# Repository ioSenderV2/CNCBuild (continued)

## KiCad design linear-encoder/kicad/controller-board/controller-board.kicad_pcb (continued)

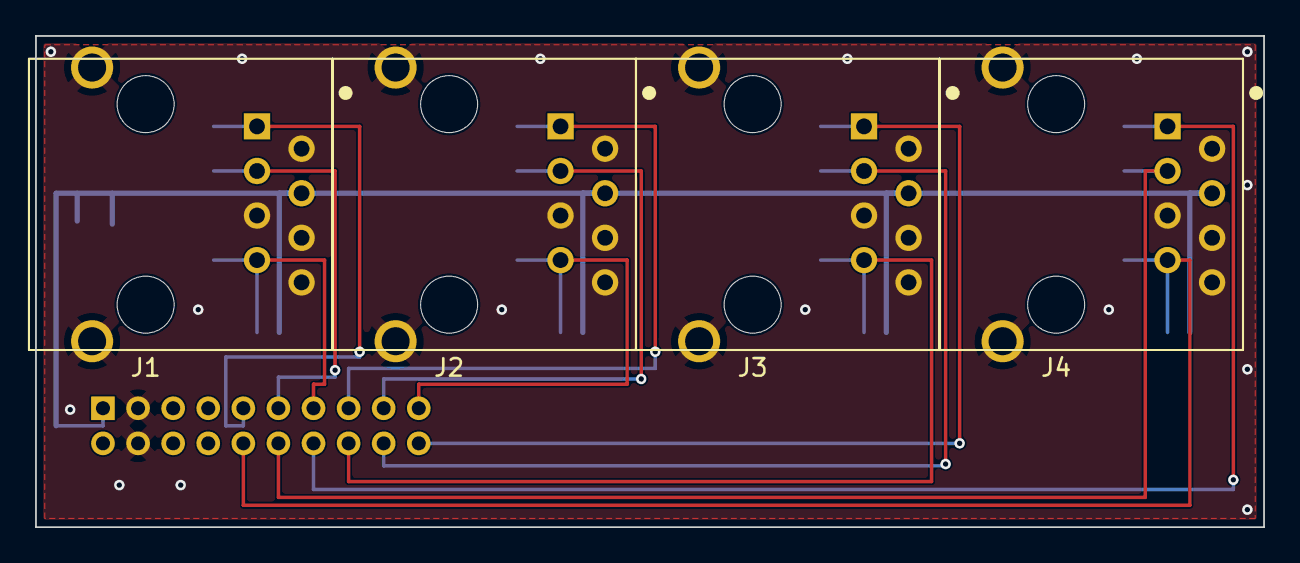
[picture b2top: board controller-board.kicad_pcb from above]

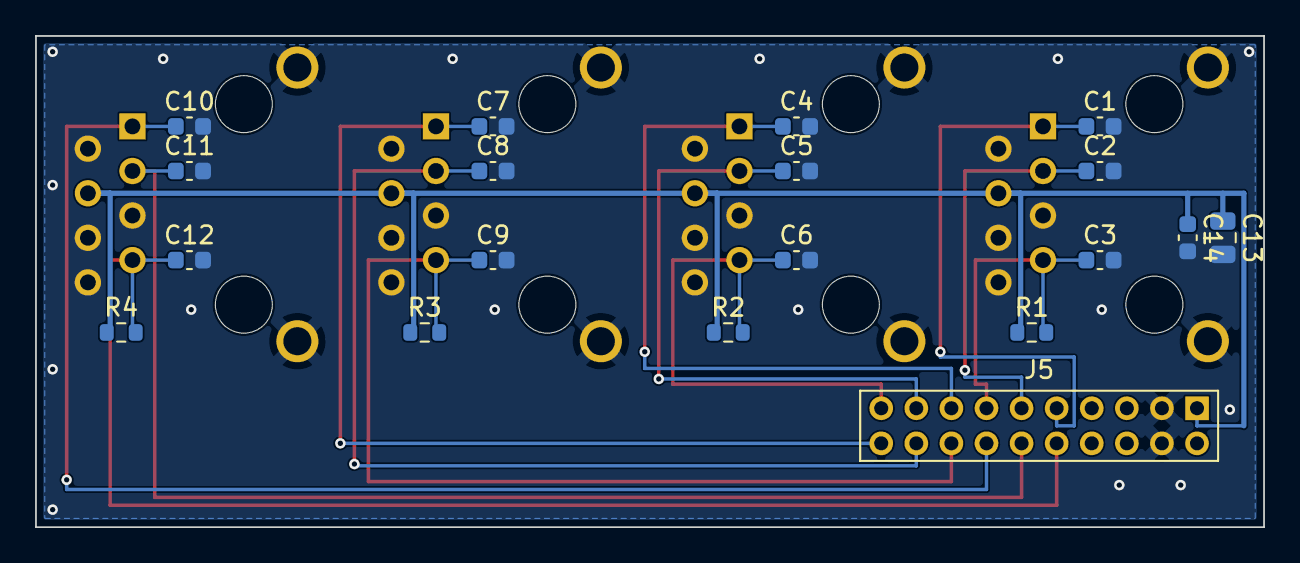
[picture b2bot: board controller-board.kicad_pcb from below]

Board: 2 copper layers, 70.0 x 28.0 mm, 23 parts (19 on the bottom side), 14 nets.

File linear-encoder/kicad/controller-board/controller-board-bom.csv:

"Refs","Value","Footprint","Qty","DNP"
"C1","1n","Capacitor_SMD:C_0603_1608Metric","1",""
"C2","1n","Capacitor_SMD:C_0603_1608Metric","1",""
"C3","1n","Capacitor_SMD:C_0603_1608Metric","1",""
"C4","1n","Capacitor_SMD:C_0603_1608Metric","1",""
"C5","1n","Capacitor_SMD:C_0603_1608Metric","1",""
"C6","1n","Capacitor_SMD:C_0603_1608Metric","1",""
"C7","1n","Capacitor_SMD:C_0603_1608Metric","1",""
"C8","1n","Capacitor_SMD:C_0603_1608Metric","1",""
"C9","1n","Capacitor_SMD:C_0603_1608Metric","1",""
"C10","1n","Capacitor_SMD:C_0603_1608Metric","1",""
"C11","1n","Capacitor_SMD:C_0603_1608Metric","1",""
"C12","1n","Capacitor_SMD:C_0603_1608Metric","1",""
"C13","10u","Capacitor_SMD:C_0805_2012Metric","1",""
"C14","100n","Capacitor_SMD:C_0603_1608Metric","1",""
"J1","RJ45 X","controller-board:RJ45_SameSky_CRJ068-1-SMT_Vertical_ShieldTied","1",""
"J2","RJ45 Y","controller-board:RJ45_SameSky_CRJ068-1-SMT_Vertical_ShieldTied","1",""
"J3","RJ45 A","controller-board:RJ45_SameSky_CRJ068-1-SMT_Vertical_ShieldTied","1",""
"J4","RJ45 Z","controller-board:RJ45_SameSky_CRJ068-1-SMT_Vertical_ShieldTied","1",""
"J5","P1 2.00mm 2x10","controller-board:PinSocket_2x10_P2.00mm_Vertical_UnderBoard","1",""
"R1","2k2","Resistor_SMD:R_0603_1608Metric","1",""
"R2","2k2","Resistor_SMD:R_0603_1608Metric","1",""
"R3","2k2","Resistor_SMD:R_0603_1608Metric","1",""
"R4","2k2","Resistor_SMD:R_0603_1608Metric","1",""

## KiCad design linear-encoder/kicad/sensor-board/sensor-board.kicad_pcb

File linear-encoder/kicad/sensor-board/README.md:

# Sensor board - KiCad

Schematic for the board described in [`../../sensor-board.md`](../../sensor-board.md).

| File | |
|---|---|
| `sensor-board.kicad_sch` | The schematic. Symbols are **embedded** (`lib_symbols`), so it needs no external libraries. |
| `sensor-board.kicad_pro` | Project wrapper. |
| `netlist.txt` | The connection list, generated from the same source as the schematic. |
| `generate.py` | The seed that produced the first version. See the warning below. |

> FLAG: **`generate.py` is already a SEED, not the source of truth - as of 2026-08-29.**
> It took one `kicad-cli sch erc` run: the tool **re-saves the schematic**, upgrading it from the
> `version 20231120` header the script writes to KiCad 10's own format (and to CRLF, which
> `.gitattributes` normalises back to LF on commit). Nobody opened Eeschema; running the checks was
> enough. **Re-running `generate.py` now overwrites whatever KiCad wrote, including any layout or
> hand edits.** Treat the `.kicad_sch` as the live document, keep the script as the record of how the
> netlist was derived, and if the design changes, edit in Eeschema and update `netlist.txt` to match.
>
> Connectivity was re-checked **after** the upgrade: all 12 nets and every node still identical, and
> all 9 `no_connect` markers intact. The format change carried the design across without loss.

## Status: verified against KiCad 10.0.5

Checked with `kicad-cli`, not just written and hoped for:

| Check | Result |
|---|---|
| Parses / loads | **Yes** - `sch erc` and `sch export netlist` both succeed |
| Netlist matches `netlist.txt` | **Exactly.** All 12 connected nets, every node identical, nothing extra or missing |
| `no_connect` coverage | **9 pins - 1, 6, 7, 10, 11, 15, 16, 17, 20** - exactly the datasheet's NC list plus Index and PWM |
| ERC violations | **12**, all one warning type - see below |

Reproduce with:

```
kicad-cli sch erc --severity-all --output erc-report.txt sensor-board.kicad_sch
kicad-cli sch export netlist --format kicadsexpr --output kicad-export.net sensor-board.kicad_sch
```

### The 12 violations are all expected

Every one is `lib_symbol_issues`: *"The current configuration does not include the symbol library
'cnc'"*. The symbols are embedded in the file rather than coming from a configured library, so KiCad
notes it. Nothing is broken - and as on the controller board the warning is arguably useful, because
those symbols **are** placeholders.

## Symbols are placeholders - swap before layout

`cnc:AS5311`, `cnc:RJ45_8_UNSHLD`, `cnc:TVS_4`, `cnc:R`, `cnc:C`, `cnc:TP` are minimal rectangles with
correct pin numbering and, on the AS5311, correct pin names from datasheet Table 1. Enough to carry
the netlist; not real parts. Before layout:

- **The RJ45 footprint is the open question, not a detail.** Unshielded, vertical, no magnetics - and
  whether it can be through-hole at all is unresolved. `../../sensor-board.md` has the height budget
  and the options. **Do not lay this board out until that is settled**, because it decides the part.
- **The AS5311 footprint is the one dimension that matters.** The datasheet's recommended land
  pattern is A 7.00, B 5.00, C 0.38, D 0.65, E 6.23 mm (rev 1.12 §9.1, Fig 18). What actually decides
  accuracy is the **Hall array position relative to the package's reference edges**, from Figure 14 -
  and that figure was read off a rendered page, so confirm those edges first.
- Expect a "no power source" ERC complaint once real power symbols are used: `+3V3` arrives through
  a passive connector pin, which is honest for a board at the end of a cable. A `PWR_FLAG` settles it.

## How it is drawn

**Connections are by net label on a short stub at each pin**, not point-to-point wires - the same
convention as the controller board, for the same reason. It reads as a fan-out list, which is what
the board is.

Net names ending `_SRC` are the chip side of a series resistor; the bare name is the cable side. So
`A_SRC` is `U1` pin 4, `A` is what reaches the jack.

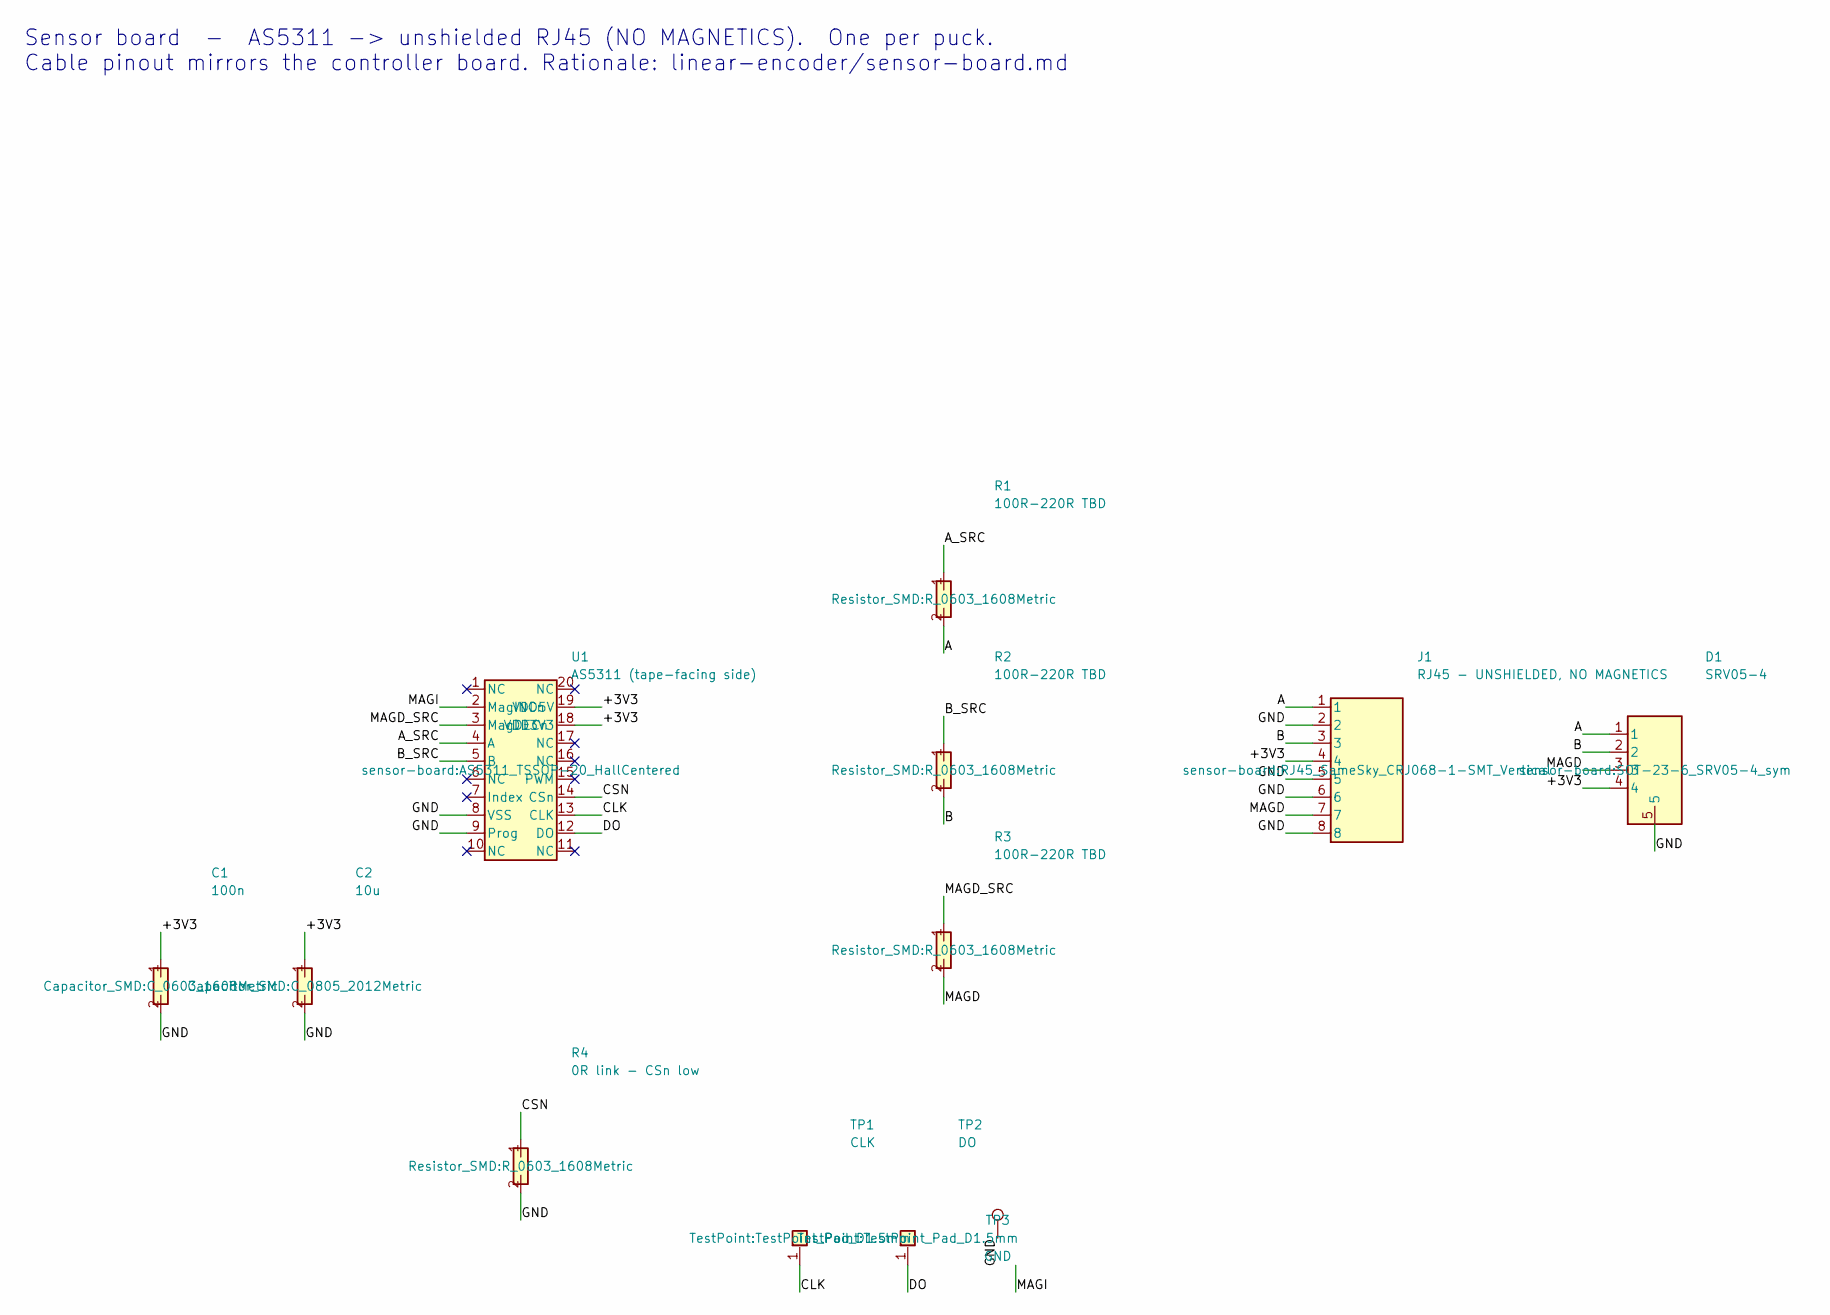
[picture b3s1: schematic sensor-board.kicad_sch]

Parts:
C1: 100n; C_0603_1608Metric
C2: 10u; C_0805_2012Metric
D1: SRV05-4; SOT-23-6_SRV05-4_sym
J1: RJ45 - UNSHIELDED, NO MAGNETICS; RJ45_SameSky_CRJ068-1-SMT_Vertical
R1, R2, R3: 100R-220R TBD; R_0603_1608Metric
R4: 0R link - CSn low; R_0603_1608Metric
TP1: CLK; TestPoint_Pad_D1.5mm
TP2: DO; TestPoint_Pad_D1.5mm
TP3: GND; TestPoint_Pad_D1.5mm
U1: AS5311 (tape-facing side); AS5311_TSSOP-20_HallCentered

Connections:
+3V3: C1.1, C2.1, D1.4, J1.4, U1.18 (VDD3V3), U1.19 (VDD5V)
A: D1.1, J1.1, R1.2
A_SRC: R1.1, U1.4 (A)
B: D1.2, J1.3, R2.2
B_SRC: R2.1, U1.5 (B)
CLK: TP1.1, U1.13 (CLK)
CSN: R4.1, U1.14 (CSn)
DO: TP2.1, U1.12 (DO)
GND: C1.2, C2.2, D1.5, J1.2, J1.5, J1.6, J1.8, R4.2, TP3.1, U1.8 (VSS), U1.9 (Prog)
MAGD: D1.3, J1.7, R3.2
MAGD_SRC: R3.1, U1.3 (MagDECn)
MAGI: U1.2 (MagINCn)

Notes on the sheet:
Sensor board - AS5311 -> unshielded RJ45 (NO MAGNETICS). One per puck. Cable pinout mirrors the controller board. Rationale: linear-encoder/sensor-board.md

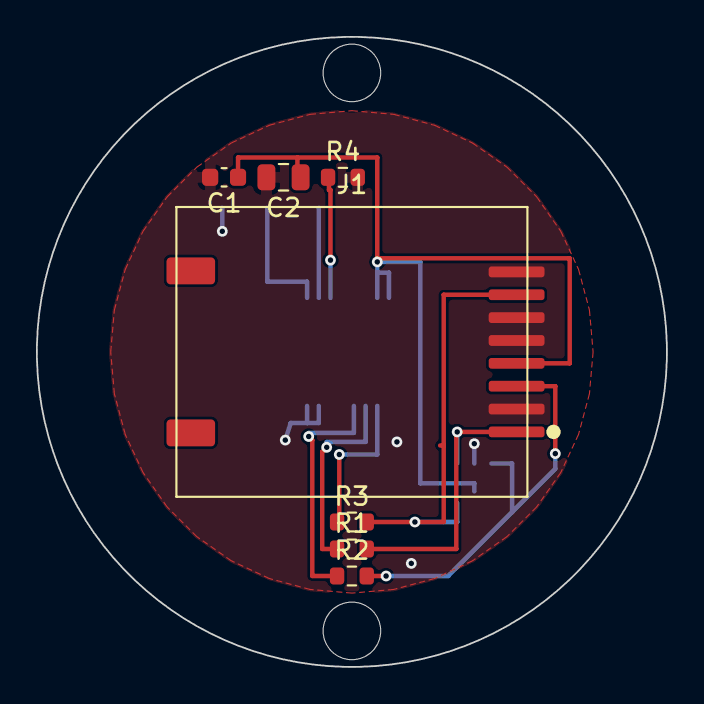
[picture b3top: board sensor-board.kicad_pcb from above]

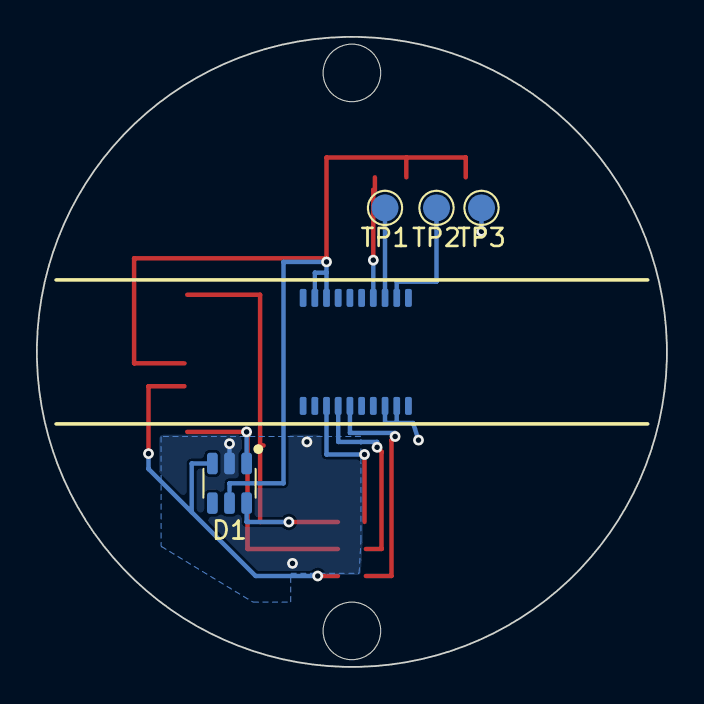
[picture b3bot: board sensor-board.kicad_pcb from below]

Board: 2 copper layers, 35.0 x 35.0 mm, 14 parts (5 on the bottom side), 11 nets.

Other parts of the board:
MH1, MH2: MountingHole_3.2mm

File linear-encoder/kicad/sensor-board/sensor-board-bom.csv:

"Refs","Value","Footprint","Qty","DNP"
"C1","100n","Capacitor_SMD:C_0603_1608Metric","1",""
"C2","10u","Capacitor_SMD:C_0805_2012Metric","1",""
"D1","SRV05-4","sensor-board:SOT-23-6_SRV05-4_sym","1",""
"J1","RJ45 - UNSHIELDED, NO MAGNETICS","sensor-board:RJ45_SameSky_CRJ068-1-SMT_Vertical","1",""
"R1","100R-220R TBD","Resistor_SMD:R_0603_1608Metric","1",""
"R2","100R-220R TBD","Resistor_SMD:R_0603_1608Metric","1",""
"R3","100R-220R TBD","Resistor_SMD:R_0603_1608Metric","1",""
"R4","0R link - CSn low","Resistor_SMD:R_0603_1608Metric","1",""
"TP1","CLK","TestPoint:TestPoint_Pad_D1.5mm","1",""
"TP2","DO","TestPoint:TestPoint_Pad_D1.5mm","1",""
"TP3","GND","TestPoint:TestPoint_Pad_D1.5mm","1",""
"U1","AS5311  (tape-facing side)","sensor-board:AS5311_TSSOP-20_HallCentered","1",""

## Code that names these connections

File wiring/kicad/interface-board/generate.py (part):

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  2x10 IDC  - ribbon to RP23 J20, mirrored pin-for-pin
  2x3  IDC  - ribbon to RP23 J24 servo alarm header, per-axis parallel
  screw terminal blocks: 12V in (from the 36V->12V buck), 12V out (to the RP23's
  power inputs), 5P limits, 4P spindle, 2P probe+door

Axis mapping: the Y1 jack drives the controller's Y, the Y2 jack drives A.

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    place("cnc:CONN_1x03", "J%d" % (i + 6), "Mini-Fit 3P - %s prox" % lab,
          125, y, rec("J%d" % (i + 6), px))

# Probe family and spindle, bottom row.
place("cnc:CONN_1x03", "J11", "Mini-Fit 3P - 3D probe",
      60, 272, rec("J11", {1: "+12V", 2: "PROBE", 3: "GND"}))
place("cnc:CONN_1x03", "J12", "Mini-Fit 3P - toolsetter",
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place("cnc:CONN_1x02", "J14", "Mini-Fit 2P - touch probe 2",
      240, 272, rec("J14", {1: "PROBE", 2: "GND"}))
place("cnc:CONN_1x04", "J15", "Mini-Fit 4P - spindle",
      300, 272, rec("J15", {1: "SPIN_EN", 2: "GND", 3: "GND", 4: "SPIN_PWM"}))

# Controller side. J16 mirrors RP23 J20 pin-for-pin (1:1 ribbon, pin 1 to pin 1).
J20_MAP = {}
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      240, 120, rec("J21", {1: "LIM_X", 2: "LIM_Y", 3: "LIM_A",
                            4: "LIM_Z", 5: "LIM_B"}))
place("cnc:TB_1x04", "J22", "TB 4P - spindle to RP23",
      240, 165, rec("J22", {1: "SPIN_EN", 2: "GND", 3: "GND", 4: "SPIN_PWM"}))
place("cnc:TB_1x02", "J23", "TB 2P - probe + door to RP23",
      240, 205, rec("J23", {1: "PROBE", 2: "DOOR"}))

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
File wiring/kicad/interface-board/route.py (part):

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# between input rows 3 and 4, each 2.5 mm west of its column's bundle. Pin 1
# (that axis's AL) reaches the AL street through a short B.Cu stub ending in
# a via ON the street line - a via fits the 0.70 bundle pitch where a 1.7 mm
# pad does not. Pin 2 is AL_X: the rail, one B.Cu run across the top half
# (nothing else uses B.Cu above corridor R), jogging over each foreign stub.
# Streets are F.Cu verticals, stubs and rail are B.Cu horizontals - they
# cross freely. Three earlier designs failed; rev-c-changes.py has the list.
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# running west on B.Cu all the way to the AL_X street's via.
# Pad row y 50.9, NOT 54.05: a pad at 54.05 sits dead-center in ROW4's jog
# band (53.05..55.25) and needs 1.2 mm of clearance either side - the first
# cut at 54.05 made every ROW4 jog near a jumper impossible and SPIN_0_10V
# could no longer reach its eastern crossing. At 50.9 the pads live inside
# ROW3's band, whose own jog corridor (37.4..39.3) is nowhere near.
# The jumpers stand VERTICAL (pin 1 over pin 2) in pockets verified against
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# The middle of ROWA - J16's column forest from x 45.1 to 68 - offers exactly
# four crossings and Rev B used all four. Which net grabs which is decided by
# candidate ordering, and a tie that breaks differently strands the last net:
# in Rev C's first routing runs SPIN_0_10V took SPIN_EN's western gap and
# SPIN_EN had nowhere left. These preferences pin each net to its proven
# Rev B crossing so the fit never depends on tie-breaks again.
SRC_PREFER = {
    "MIST_A": 59.15,
    "MIST_B": 61.69,
    "SPIN_EN": 56.61,
    "SPIN_0_10V": 69.3,
}


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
